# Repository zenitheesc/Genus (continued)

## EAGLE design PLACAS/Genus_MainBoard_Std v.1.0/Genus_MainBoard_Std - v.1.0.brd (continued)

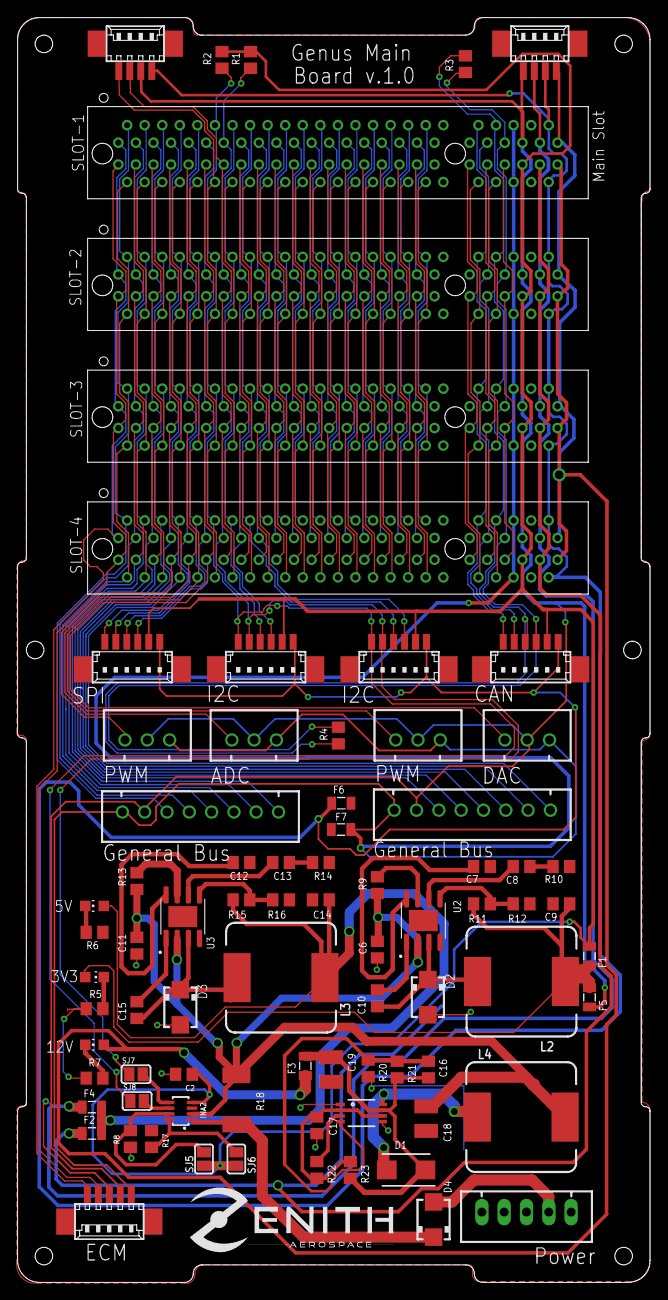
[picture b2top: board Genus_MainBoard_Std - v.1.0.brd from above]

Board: 2 copper layers, 72.0 x 144.0 mm, 80 parts (0 on the bottom side), 121 nets.

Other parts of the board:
SLOT-1, SLOT-2, SLOT-3, SLOT-4: PCIE-098-02-X-D-TH

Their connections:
3V3_A: SLOT-1.A5, SLOT-2.A5, SLOT-3.A5, SLOT-4.A5; also elsewhere on the board
3V3_B: SLOT-1.B5, SLOT-2.B5, SLOT-3.B5, SLOT-4.B5; also elsewhere on the board
5V_A: SLOT-1.A3, SLOT-2.A3, SLOT-3.A3, SLOT-4.A3; also elsewhere on the board
5V_B: SLOT-1.B3, SLOT-2.B3, SLOT-3.B3, SLOT-4.B3; also elsewhere on the board
12V: SLOT-1.A1, SLOT-1.B1, SLOT-2.A1, SLOT-2.B1, SLOT-3.A1, SLOT-3.B1, SLOT-4.A1, SLOT-4.B1; also elsewhere on the board
ADC_1: SLOT-1.B37, SLOT-2.B37, SLOT-3.B37, SLOT-4.B37; also elsewhere on the board
ADC_2: SLOT-1.A37, SLOT-2.A37, SLOT-3.A37, SLOT-4.A37; also elsewhere on the board
ADC_3: SLOT-1.B38, SLOT-2.B38, SLOT-3.B38, SLOT-4.B38; also elsewhere on the board
ADC_4: SLOT-1.A38, SLOT-2.A38, SLOT-3.A38, SLOT-4.A38; also elsewhere on the board
ADC_5: SLOT-1.B39, SLOT-2.B39, SLOT-3.B39, SLOT-4.B39; also elsewhere on the board
ADC_6: SLOT-1.A39, SLOT-2.A39, SLOT-3.A39, SLOT-4.A39; also elsewhere on the board
ADC_7: SLOT-1.B40, SLOT-2.B40, SLOT-3.B40, SLOT-4.B40; also elsewhere on the board
ADC_8: SLOT-1.A40, SLOT-2.A40, SLOT-3.A40, SLOT-4.A40; also elsewhere on the board
ADC_9: SLOT-1.B41, SLOT-2.B41, SLOT-3.B41, SLOT-4.B41; also elsewhere on the board
ADC_10: SLOT-1.A41, SLOT-2.A41, SLOT-3.A41, SLOT-4.A41; also elsewhere on the board
ADC_11: SLOT-1.B42, SLOT-2.B42, SLOT-3.B42, SLOT-4.B42; also elsewhere on the board
ADC_12: SLOT-1.A42, SLOT-2.A42, SLOT-3.A42, SLOT-4.A42; also elsewhere on the board
CAN_HIGH: SLOT-1.B7, SLOT-2.B7, SLOT-3.B7, SLOT-4.B7; also elsewhere on the board
CAN_LOW: SLOT-1.B8, SLOT-2.B8, SLOT-3.B8, SLOT-4.B8; also elsewhere on the board
DAC_1: SLOT-1.B28, SLOT-2.B28, SLOT-3.B28, SLOT-4.B28
DAC_2: SLOT-1.A28, SLOT-2.A28, SLOT-3.A28, SLOT-4.A28
DAC_3: SLOT-1.B29, SLOT-2.B29, SLOT-3.B29, SLOT-4.B29
DAC_4: SLOT-1.A29, SLOT-2.A29, SLOT-3.A29, SLOT-4.A29
DAC_5: SLOT-1.B30, SLOT-2.B30, SLOT-3.B30, SLOT-4.B30
DAC_6: SLOT-1.A30, SLOT-2.A30, SLOT-3.A30, SLOT-4.A30
GEP_1: SLOT-1.B48, SLOT-2.B48, SLOT-3.B48, SLOT-4.B48; also elsewhere on the board
GEP_2: SLOT-1.A48, SLOT-2.A48, SLOT-3.A48, SLOT-4.A48; also elsewhere on the board
GEP_3: SLOT-1.B49, SLOT-2.B49, SLOT-3.B49, SLOT-4.B49; also elsewhere on the board
GEP_4: SLOT-1.A49, SLOT-2.A49, SLOT-3.A49, SLOT-4.A49; also elsewhere on the board
GEP_5: SLOT-1.A7, SLOT-2.A7, SLOT-3.A7, SLOT-4.A7
GEP_6: SLOT-1.A8, SLOT-2.A8, SLOT-3.A8, SLOT-4.A8
GEP_7: SLOT-1.A9, SLOT-2.A9, SLOT-3.A9, SLOT-4.A9
GEP_8: SLOT-1.A10, SLOT-2.A10, SLOT-3.A10, SLOT-4.A10
GEP_9: SLOT-1.A11, SLOT-2.A11, SLOT-3.A11, SLOT-4.A11
GIP_1: SLOT-1.B43, SLOT-2.B43, SLOT-3.B43, SLOT-4.B43; also elsewhere on the board
GIP_2: SLOT-1.A43, SLOT-2.A43, SLOT-3.A43, SLOT-4.A43; also elsewhere on the board
GIP_3: SLOT-1.B44, SLOT-2.B44, SLOT-3.B44, SLOT-4.B44; also elsewhere on the board
GIP_4: SLOT-1.A44, SLOT-2.A44, SLOT-3.A44, SLOT-4.A44; also elsewhere on the board
GIP_5: SLOT-1.B45, SLOT-2.B45, SLOT-3.B45, SLOT-4.B45; also elsewhere on the board
GIP_6: SLOT-1.A45, SLOT-2.A45, SLOT-3.A45, SLOT-4.A45; also elsewhere on the board
GIP_7: SLOT-1.B46, SLOT-2.B46, SLOT-3.B46, SLOT-4.B46; also elsewhere on the board
GIP_8: SLOT-1.A46, SLOT-2.A46, SLOT-3.A46, SLOT-4.A46; also elsewhere on the board
GIP_9: SLOT-1.B47, SLOT-2.B47, SLOT-3.B47, SLOT-4.B47; also elsewhere on the board
GIP_10: SLOT-1.A47, SLOT-2.A47, SLOT-3.A47, SLOT-4.A47; also elsewhere on the board
GND: SLOT-1.A4, SLOT-1.B4, SLOT-2.A4, SLOT-2.B4, SLOT-3.A4, SLOT-3.B4, SLOT-4.A4, SLOT-4.B4; also elsewhere on the board
GND_1: SLOT-1.A2, SLOT-1.B2, SLOT-2.A2, SLOT-2.B2, SLOT-3.A2, SLOT-3.B2, SLOT-4.A2, SLOT-4.B2; also elsewhere on the board
GND_3: SLOT-1.A6, SLOT-1.B6, SLOT-2.A6, SLOT-2.B6, SLOT-3.A6, SLOT-3.B6, SLOT-4.A6, SLOT-4.B6; also elsewhere on the board
INT_1: SLOT-1.B16, SLOT-2.B16, SLOT-3.B16, SLOT-4.B16
INT_1_(E): SLOT-1.A22, SLOT-2.A22, SLOT-3.A22, SLOT-4.A22
INT_2: SLOT-1.A16, SLOT-2.A16, SLOT-3.A16, SLOT-4.A16
INT_2_(E): SLOT-1.A23, SLOT-2.A23, SLOT-3.A23, SLOT-4.A23
INT_3: SLOT-1.B17, SLOT-2.B17, SLOT-3.B17, SLOT-4.B17
INT_3_(E): SLOT-1.A24, SLOT-2.A24, SLOT-3.A24, SLOT-4.A24
INT_4: SLOT-1.A17, SLOT-2.A17, SLOT-3.A17, SLOT-4.A17
INT_4_(E): SLOT-1.A25, SLOT-2.A25, SLOT-3.A25, SLOT-4.A25
INT_5: SLOT-1.B18, SLOT-2.B18, SLOT-3.B18, SLOT-4.B18
INT_5_(E): SLOT-1.A26, SLOT-2.A26, SLOT-3.A26, SLOT-4.A26
INT_6: SLOT-1.A18, SLOT-2.A18, SLOT-3.A18, SLOT-4.A18
INT_6_(E): SLOT-1.A27, SLOT-2.A27, SLOT-3.A27, SLOT-4.A27
INT_7: SLOT-1.B19, SLOT-2.B19, SLOT-3.B19, SLOT-4.B19
INT_8: SLOT-1.A19, SLOT-2.A19, SLOT-3.A19, SLOT-4.A19
INT_9: SLOT-1.B20, SLOT-2.B20, SLOT-3.B20, SLOT-4.B20
INT_10: SLOT-1.A20, SLOT-2.A20, SLOT-3.A20, SLOT-4.A20
INT_11: SLOT-1.B21, SLOT-2.B21, SLOT-3.B21, SLOT-4.B21
INT_12: SLOT-1.A21, SLOT-2.A21, SLOT-3.A21, SLOT-4.A21
MISO_1: SLOT-1.B15, SLOT-2.B15, SLOT-3.B15, SLOT-4.B15
MISO_2: SLOT-1.B22, SLOT-2.B22, SLOT-3.B22, SLOT-4.B22
MOSI_1: SLOT-1.A14, SLOT-2.A14, SLOT-3.A14, SLOT-4.A14
MOSI_2: SLOT-1.B23, SLOT-2.B23, SLOT-3.B23, SLOT-4.B23
PWM_1: SLOT-1.B31, SLOT-2.B31, SLOT-3.B31, SLOT-4.B31
PWM_2: SLOT-1.A31, SLOT-2.A31, SLOT-3.A31, SLOT-4.A31
PWM_3: SLOT-1.B32, SLOT-2.B32, SLOT-3.B32, SLOT-4.B32
PWM_4: SLOT-1.A32, SLOT-2.A32, SLOT-3.A32, SLOT-4.A32
PWM_5: SLOT-1.B33, SLOT-2.B33, SLOT-3.B33, SLOT-4.B33; also elsewhere on the board
PWM_6: SLOT-1.A33, SLOT-2.A33, SLOT-3.A33, SLOT-4.A33
PWM_7: SLOT-1.B34, SLOT-2.B34, SLOT-3.B34, SLOT-4.B34; also elsewhere on the board
PWM_8: SLOT-1.A34, SLOT-2.A34, SLOT-3.A34, SLOT-4.A34
PWM_9: SLOT-1.B35, SLOT-2.B35, SLOT-3.B35, SLOT-4.B35; also elsewhere on the board
PWM_10: SLOT-1.A35, SLOT-2.A35, SLOT-3.A35, SLOT-4.A35
PWM_11: SLOT-1.B36, SLOT-2.B36, SLOT-3.B36, SLOT-4.B36; also elsewhere on the board
PWM_12: SLOT-1.A36, SLOT-2.A36, SLOT-3.A36, SLOT-4.A36
SCLK_1: SLOT-1.B14, SLOT-2.B14, SLOT-3.B14, SLOT-4.B14
SCLK_2: SLOT-1.B24, SLOT-2.B24, SLOT-3.B24, SLOT-4.B24
SCL_1: SLOT-1.B9, SLOT-2.B9, SLOT-3.B9, SLOT-4.B9; also elsewhere on the board
SCL_2: SLOT-1.B27, SLOT-2.B27, SLOT-3.B27, SLOT-4.B27
SDA_1: SLOT-1.B10, SLOT-2.B10, SLOT-3.B10, SLOT-4.B10; also elsewhere on the board
SDA_2: SLOT-1.B26, SLOT-2.B26, SLOT-3.B26, SLOT-4.B26
SS_1: SLOT-1.A15, SLOT-2.A15, SLOT-3.A15, SLOT-4.A15
SS_2: SLOT-1.B25, SLOT-2.B25, SLOT-3.B25, SLOT-4.B25

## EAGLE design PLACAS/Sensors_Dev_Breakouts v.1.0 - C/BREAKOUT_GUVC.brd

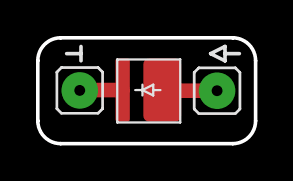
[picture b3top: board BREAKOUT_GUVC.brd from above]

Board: 2 copper layers, 12.1 x 5.9 mm, 3 parts (0 on the bottom side), 2 nets.

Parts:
1, 2: JP0
U$1: GUVC-S10GD; GUVD-S10GD

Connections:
unnamed: 1.1, U$1.ANODE
unnamed: 2.1, U$1.CATHODE

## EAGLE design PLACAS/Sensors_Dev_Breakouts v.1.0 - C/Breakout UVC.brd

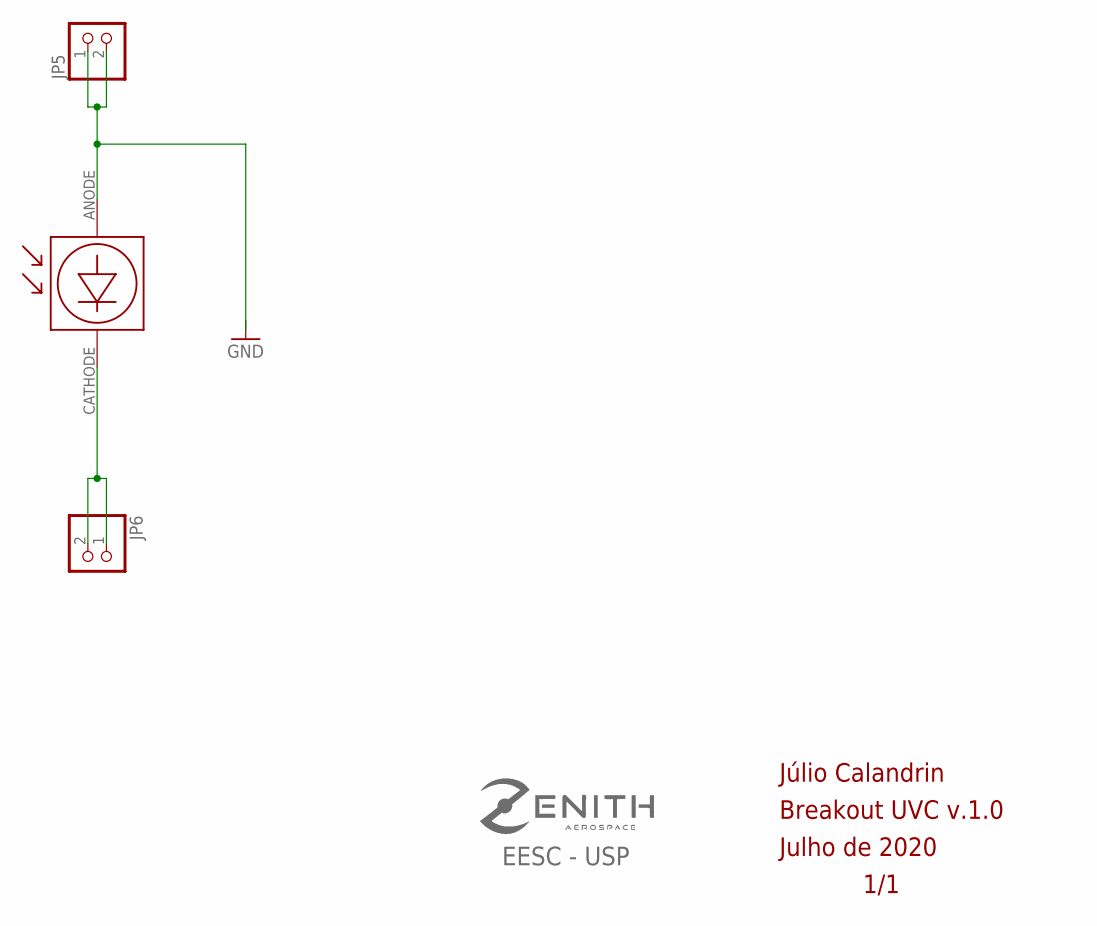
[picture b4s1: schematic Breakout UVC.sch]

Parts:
JP5, JP6: PINHD-1X2; 1X02
U$1: GUVC-S10GD; GUV_C

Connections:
GND: JP5.1, JP5.2, U$1.ANODE
unnamed: JP6.1, JP6.2, U$1.CATHODE

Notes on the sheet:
EESC - USP
Júlio Calandrin
Julho de 2020
1/1
Breakout UVC v.1.0

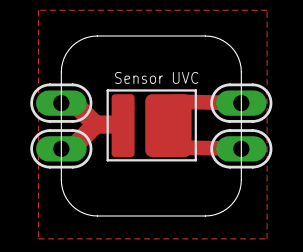
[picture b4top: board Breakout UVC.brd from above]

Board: 2 copper layers, 10.0 x 10.0 mm, 3 parts (0 on the bottom side), 2 nets.

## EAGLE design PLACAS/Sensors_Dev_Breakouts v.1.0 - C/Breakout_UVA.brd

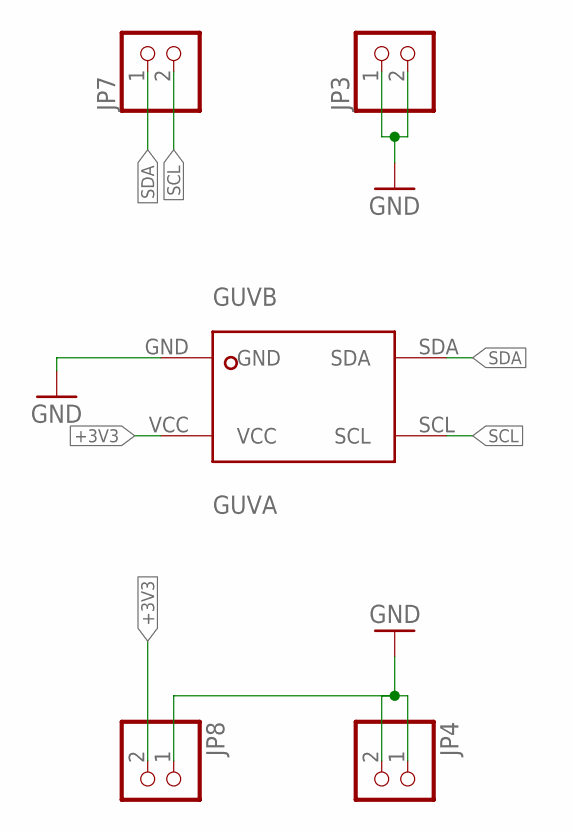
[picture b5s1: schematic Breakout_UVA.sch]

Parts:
GUVB: GUVA; GUV_A/B
JP3, JP4, JP7, JP8: PINHD-1X2; 1X02(PAD_REDUZIDO)

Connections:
+3V3: GUVB.VCC, JP8.2
GND: GUVB.GND, JP3.1, JP3.2, JP4.1, JP4.2, JP8.1
SCL: GUVB.SCL, JP7.2
SDA: GUVB.SDA, JP7.1

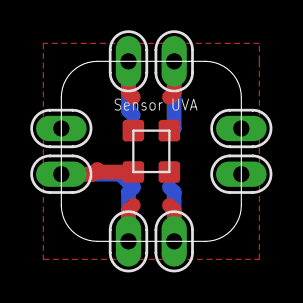
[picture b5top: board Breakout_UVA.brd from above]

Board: 2 copper layers, 10.0 x 10.0 mm, 5 parts (0 on the bottom side), 4 nets.

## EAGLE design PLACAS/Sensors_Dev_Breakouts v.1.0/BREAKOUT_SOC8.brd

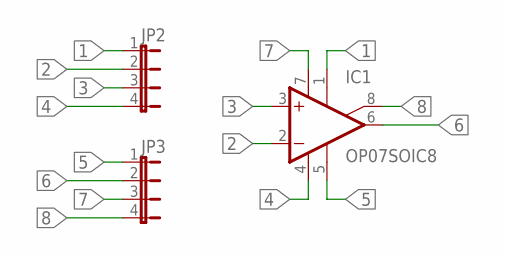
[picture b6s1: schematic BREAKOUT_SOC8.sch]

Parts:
IC1: OP07SOIC8; SOIC8
JP2, JP3: JP4E; JP4

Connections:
1: IC1.1 (ON1), JP2.1
2: IC1.2 (-IN), JP2.2
3: IC1.3 (+IN), JP2.3
4: IC1.4 (V-), JP2.4
5: IC1.5 (OPT), JP3.1
6: IC1.6 (OUT), JP3.2
7: IC1.7 (V+), JP3.3
8: IC1.8 (ON2), JP3.4

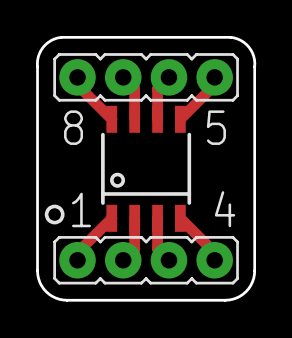
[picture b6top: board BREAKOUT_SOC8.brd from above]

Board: 2 copper layers, 12.1 x 14.6 mm, 3 parts (0 on the bottom side), 8 nets.

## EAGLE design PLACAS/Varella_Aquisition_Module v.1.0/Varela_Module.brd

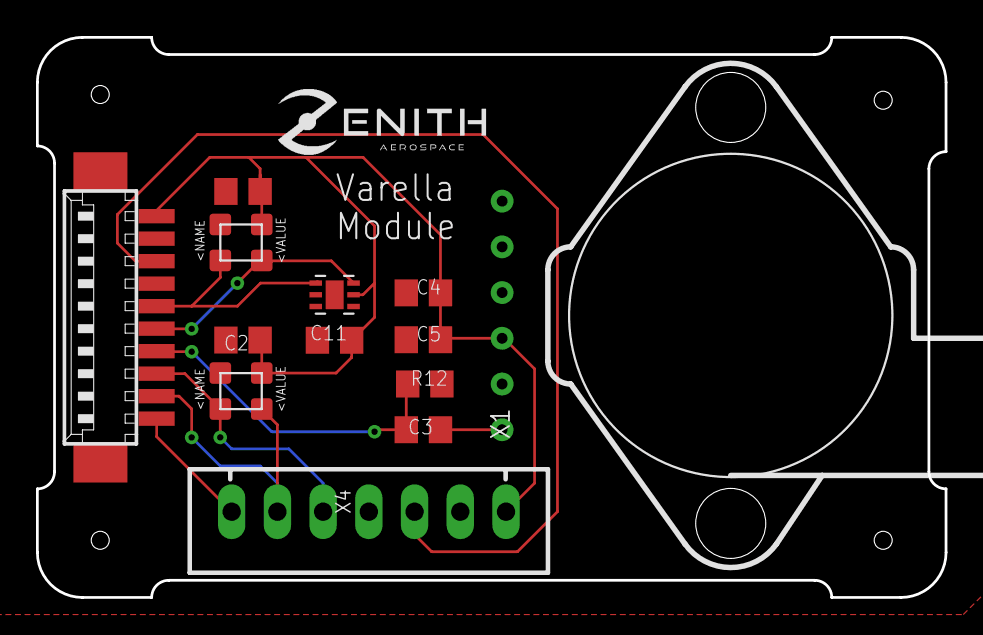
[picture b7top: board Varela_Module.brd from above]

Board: 2 copper layers, 50.5 x 31.1 mm, 13 parts (0 on the bottom side), 10 nets.

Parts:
C1, C2, C11: 100n; C0805
C3: 330n; C0805
C4: 1000n; C0805
C5: 10n; C0805
I2C1, I2C2: GUVA-C32SM
R12: 750; R0805
U$1: HDC1080; TI-S-PWSON-N6
X1: MPX5700
X2: 53261-10
X4: JST-XH-07-PIN-LONG-PAD; JST-XH-07-PACKAGE-LONG-PAD

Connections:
+3V3: C1.1, C2.1, C4.2, C5.2, C11.1, I2C1.VCC, I2C2.VCC, U$1.5, X1.P$3, X2.1, X4.1
+5V: X2.3, X4.3
GND: C1.2, C2.2, C3.1, C4.1, C5.1, C11.2, I2C1.GND, I2C2.GND, U$1.2, X1.P$2, X2.2, X2.4, X4.2, X4.4
unnamed: R12.2, X1.P$1
SCL_1: I2C1.SCL, U$1.6, X2.6
SCL_2: I2C2.SCL, X2.9, X4.6
SDA_1: I2C1.SDA, U$1.1, X2.5
SDA_2: I2C2.SDA, X2.8, X4.5
V_OUT: X2.10, X4.7
V_PRESSURE: C3.2, R12.1, X2.7
